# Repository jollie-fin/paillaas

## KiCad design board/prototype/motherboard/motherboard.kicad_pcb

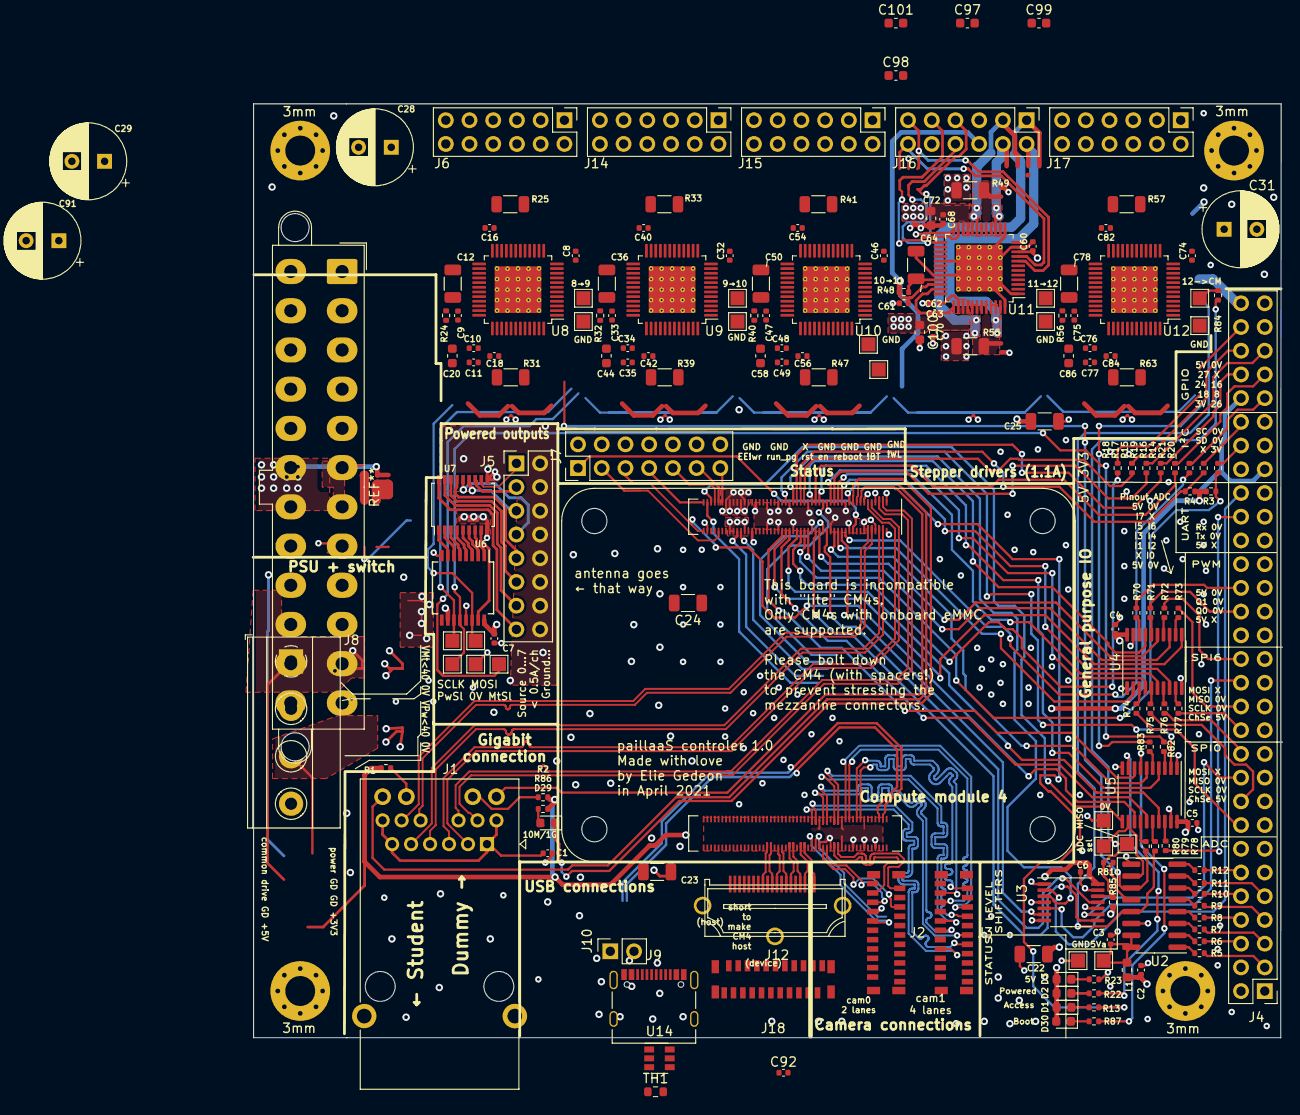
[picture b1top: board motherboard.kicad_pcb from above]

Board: 4 copper layers, 110.0 x 100.0 mm, 177 parts (0 on the bottom side), 260 nets.

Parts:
C1, C2, C3, C4, C5, C6, C7, C8, C11, C16, C18, C32, C35, C40, C42, C46, C49, C54, C56, C60, C63, C68, C70, C74, C77, C82, C84: 100n; C_0402_1005Metric
C9, C33, C47, C61, C75: 1u; C_0402_1005Metric
C10, C34, C48, C62, C76: 22n; C_0402_1005Metric
C12, C22, C23, C24, C25, C36, C50, C64, C78: 10u; C_1206_3216Metric
C20, C44, C58, C72, C86, C97, C98, C99, C100, C101: 1u; C_0603_1608Metric
C28, C29, C31, C91: 100u; CP_Radial_D8.0mm_P3.50mm
C92: 10n; C_0402_1005Metric
D1: GREEN; LED_0603_1608Metric
D2: RED; LED_0603_1608Metric
D3: BLUE; LED_0603_1608Metric
D29: LED; LED_0603_1608Metric
D30: YELLOW; LED_0603_1608Metric
H1, H2, H3, H4: MountingHole_Pad; MountingHole_3.2mm_M3_Pad_Via
J1: JK0654218Z; RJ45_Pulse_JK0654219NL_Horizontal
J2, J3, J18: Conn_01x22_MountingPin; 5019512230_1x22-1MP_P0.5mm_Vertical
J4: Conn_02x30_Odd_Even; PinHeader_2x30_P2.54mm_Vertical
J5: Conn_02x08_Odd_Even; PinHeader_2x08_P2.54mm_Vertical
J6, J14, J15, J16, J17: pin_header_02x06; PinHeader_2x06_P2.54mm_Vertical
J7: Conn_02x07_Odd_Even; PinHeader_2x07_P2.54mm_Vertical
J8: Conn_01x04; TerminalBlock_Phoenix_MKDS-1,5-4-5.08_1x04_P5.08mm_Horizont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
J9: USB_C_Receptacle_USB2.0; USB_C_Receptacle_Palconn_UTC16-G
J10: Conn_01x02; PinSocket_1x02_P2.54mm_Vertical
J12: HDMI_A; HDMI_vertical_476591102
L1: 15uH; L_0603_1608Metric
R1, R2, R86: 470; R_0402_1005Metric
R3, R4: 1K8; R_0402_1005Metric
R5, R6, R7, R8, R9, R10, R11, R12, R14, R15, R16, R17, R18, R19, R20, R21, R70, R71, R72, R73, R74, R75, R76, R77, R78: 100; R_0402_1005Metric
R13, R22, R23, R87: 4K7; R_0402_1005Metric
R24, R32, R40, R48, R56: 10; R_0402_1005Metric
R25, R31, R33, R39, R41, R47, R49, R55, R57, R63: 0.21; R_1206_3216Metric
R79, R80, R81, R82, R83, R84: 30; R_0402_1005Metric
R85: 10k; R_0402_1005Metric
TH1: Thermistor_PTC; R_0603_1608Metric
TP1, TP2, TP3, TP4, TP5, TP6, TP7, TP8, TP9, TP10, TP11, TP20, TP21, TP23, TP24, TP25, TP26, TP27, TP28, TP29: TestPoint; TestPoint_Pad_1.5x1.5mm
U1: Compute_Module_4_Functional; Raspberry-Pi-4-Compute-Module
U2: MCP3008; SOIC-16_3.9x9.9mm_P1.27mm
U3: 74LVC125; TSSOP-14_4.4x5mm_P0.65mm
U4, U5: 74HCT244; TSSOP-20_4.4x6.5mm_P0.65mm
U6: 74HC595; SSOP-16_5.3x6.2mm_P0.65mm
U7: TBD62783A; SSOP-18_4.4x6.5mm_P0.65mm
U8, U9, U10, U11, U12: TMC5130A-TA; TQFP-48-1EP_7x7mm_P0.5mm_EP5x5mm_ThermalVias
U14: SN65220; SOT-23-6

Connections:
+3V3: C6.1, C92.1, J2.22, J3.22, J4.45, J4.52, J18.22, R1.2, R2.2, R3.1, R4.1, R86.2, U1.78, U1.84, U1.86, U3.14
+5V: C2.1, C4.1, C5.1, C7.1, C8.1, C9.1, C22.1, C23.1, C24.1, C25.1, C32.1, C33.1, C46.1, C47.1, C60.1, C61.1, C74.1, C75.1, D1.2, D2.2, D3.2, D30.2, J4.2, J4.14, J4.15, J4.23, J4.32, J4.38, J4.40, J4.60, J6.6, J8.4, J10.1, J12.18, J14.6, J15.6, J16.6, J17.6, L1.2, R24.1, R32.1, R40.1, R48.1, R56.1, R85.1, U1.77, U1.79, U1.81, U1.83, U1.85, U1.87, U4.20, U5.20, U6.10, U6.16, U8.10, U8.34, U9.10, U9.34, U10.10, U10.34, U11.10, U11.34, U12.10, U12.34
/CAM_GPIO: J2.17, J3.17, U1.97
/GPIO/ACT_LED: R13.2, U1.21
/GPIO/AIN0: R5.1, U2.1
/GPIO/AIN0P: J4.3, R5.2
/GPIO/AIN1: R6.1, U2.2
/GPIO/AIN1P: J4.6, R6.2
/GPIO/AIN2: R7.1, U2.3
/GPIO/AIN2P: J4.5, R7.2
/GPIO/AIN3: R8.1, U2.4
/GPIO/AIN3P: J4.8, R8.2
/GPIO/AIN4: R9.1, U2.5
/GPIO/AIN4P: J4.7, R9.2
/GPIO/AIN5: R10.1, U2.6
/GPIO/AIN5P: J4.10, R10.2
/GPIO/AIN6: R11.1, U2.7
/GPIO/AIN6P: J4.9, R11.2
/GPIO/AIN7: R12.1, U2.8
/GPIO/AIN7P: J4.12, R12.2
/GPIO/AIN_SELECT_3V: U1.58, U5.8
/GPIO/AIN_SELECT_5V: TP5.1, U2.10, U5.12
/GPIO/CS0: U1.41, U4.17
/GPIO/CS0P: J4.16, R74.2
/GPIO/CS6: U1.56, U4.11
/GPIO/CS6P: J4.24, R77.2
/GPIO/GPIO8: R16.1, U1.39
/GPIO/GPIO8P: J4.53, R16.2
/GPIO/GPIO16: R15.1, U1.29
/GPIO/GPIO16P: J4.55, R15.2
/GPIO/GPIO18: R19.1, U1.49
/GPIO/GPIO18P: J4.54, R19.2
/GPIO/GPIO24: R17.1, U1.45
/GPIO/GPIO24P: J4.56, R17.2
/GPIO/GPIO26: R14.1, U1.24
/GPIO/GPIO26P: J4.51, R14.2
/GPIO/GPIO27: R18.1, U1.48
/GPIO/GPIO27P: J4.58, R18.2
/GPIO/MISO: R81.1, R84.2, R85.2, TP2.1, U3.12
/GPIO/MISO0: U1.40, U3.8
/GPIO/MISO0P: J4.20, U3.9
/GPIO/MISO4_3V: U1.34, U3.11
/GPIO/MISO6: U1.26, U3.6
/GPIO/MISO6P: J4.28, U3.5
/GPIO/MOSI: R80.2, TP4.1, U2.11, U6.14, U8.5
/GPIO/MOSI0: U1.44, U4.13
/GPIO/MOSI0P: J4.22, R76.2
/GPIO/MOSI4_3V: U1.30, U5.6
/GPIO/MOSI6: U1.27, U4.6
/GPIO/MOSI6P: J4.30, R72.2
/GPIO/MOTOR_SELECT: R83.2, TP7.1, U8.3, U9.3, U10.3, U11.3, U12.3
/GPIO/MOTOR_SELECT_3V: U1.54, U5.15
/GPIO/POWERED: R22.2, U5.9
/GPIO/POWER_SELECT: R82.2, TP21.1, U6.12
/GPIO/POWER_SELECT_3V: U1.50, U5.17
/GPIO/PWM0: U1.31, U4.4
/GPIO/PWM0P: J4.34, R71.2
/GPIO/PWM1: U1.28, U4.2
/GPIO/PWM1P: J4.36, R70.2
/GPIO/RxD0: U1.51, U3.3
/GPIO/RxD0P: J4.44, U3.2
/GPIO/SCL6: R4.2, R21.1, U1.47
/GPIO/SCL6P: J4.50, R21.2
/GPIO/SCLK: R79.2, TP3.1, U2.13, U6.11, U8.4, U9.4, U10.4, U11.4, U12.4
/GPIO/SCLK0: U1.38, U4.15
/GPIO/SCLK0P: J4.18, R75.2
/GPIO/SCLK4_3V: U1.37, U5.4
/GPIO/SCLK6: U1.25, U4.8
/GPIO/SCLK6P: J4.26, R73.2
/GPIO/SDA6: R3.2, R20.1, U1.46
/GPIO/SDA6P: J4.48, R20.2
/GPIO/TxD0: U1.55, U5.2
/GPIO/TxD0P: J4.42, R78.2
/GPIO/nEXTRST: J7.5, U1.100, U5.13
/GPIO/nEXTRST_pow: R87.2, U5.7
/SCL0: J3.20, J18.20, U1.80
/SCL1: J2.20, U1.35
/SDA0: J3.21, J18.21, U1.82
/SDA1: J2.21, U1.36
/camera/CAM0C+: J2.9, U1.142
/camera/CAM0C-: J2.8, U1.140
/camera/CAM0D0+: J2.3, U1.130
/camera/CAM0D0-: J2.2, U1.128
/camera/CAM0D1+: J2.6, U1.136
/camera/CAM0D1-: J2.5, U1.134
/camera/CAM1C+: J3.9, U1.129
/camera/CAM1C-: J3.8, U1.127
/camera/CAM1D0+: J3.3, U1.117
/camera/CAM1D0-: J3.2, U1.115
/camera/CAM1D1+: J3.6, U1.123
/camera/CAM1D1-: J3.5, U1.121
/camera/CAM1D2+: J3.12, U1.135
/camera/CAM1D2-: J3.11, U1.133
/camera/CAM1D3+: J3.15, U1.141
/camera/CAM1D3-: J3.14, U1.139
/cm4/BT_disable: J7.11, U1.91
/cm4/EEPROMprotect: J7.1, U1.20
/cm4/LED_Pwr: U1.95, U5.11
/cm4/USB+: J9.A6, J9.B6, U1.105, U14.6
/cm4/USB-: J9.A7, J9.B7, U1.103, U14.4
/cm4/WL_disable: J7.13, U1.89
/cm4/global_en: J7.7, U1.99
/cm4/rpireboot: J7.9, U1.93
/cm4/run_pg: J7.3, U1.92
/display/DSI1C+: J18.9, U1.189
/display/DSI1C-: J18.8, U1.187
/display/DSI1D0+: J18.3, U1.177
/display/DSI1D0-: J18.2, U1.175
/display/DSI1D1+: J18.6, U1.183
/display/DSI1D1-: J18.5, U1.181
/display/DSI1D2+: J18.12, U1.194
/display/DSI1D2-: J18.11, U1.193
/display/DSI1D3+: J18.15, U1.196
/display/DSI1D3-: J18.14, U1.195
/display/HDMI_0+: J12.7, U1.158
/display/HDMI_0-: J12.9, U1.160
/display/HDMI_1+: J12.4, U1.152
/display/HDMI_1-: J12.6, U1.154
/display/HDMI_2+: J12.1, U1.146
/display/HDMI_2-: J12.3, U1.148
/display/HDMI_C+: J12.10, U1.164
/display/HDMI_C-: J12.12, U1.166
/display/HDMI_CEC: J12.13, U1.149
/display/HDMI_HOT: J12.19, U1.143
/display/HDMI_SCL: J12.16, U1.147
/display/HDMI_SDA: J12.15, U1.145
/ethernet/ETH_0+: J1.11, U1.12
/ethernet/ETH_0-: J1.10, U1.10
/ethernet/ETH_1+: J1.4, U1.4
/ethernet/ETH_1-: J1.5, U1.6
/ethernet/ETH_2+: J1.3, U1.11
/ethernet/ETH_2-: J1.2, U1.9
/ethernet/ETH_3+: J1.8, U1.3
/ethernet/ETH_3-: J1.9, U1.5
/ethernet/ETH_LED_green: J1.13, U1.15
/ethernet/ETH_LED_yellow: J1.16, U1.17
/powerIO/OUT0: U6.15, U7.8
/powerIO/OUT1: U6.1, U7.7
/powerIO/OUT2: U6.2, U7.6
/powerIO/OUT3: U6.3, U7.5
/powerIO/OUT4: U6.4, U7.4
/powerIO/OUT5: U6.5, U7.3
/powerIO/OUT6: U6.6, U7.2
/powerIO/OUT7: U6.7, U7.1
/powerIO/SRC0: J5.15, U7.18
/powerIO/SRC1: J5.13, U7.17
/powerIO/SRC2: J5.11, U7.16
/powerIO/SRC3: J5.9, U7.15
/powerIO/SRC4: J5.7, U7.14
/powerIO/SRC5: J5.5, U7.13
/powerIO/SRC6: J5.3, U7.12
/powerIO/SRC7: J5.1, U7.11
/powerIO/motorU8/BRA: R31.1, U8.44
/powerIO/motorU8/BRB: R25.1, U8.17
/powerIO/motorU8/ENCA: J6.8, U8.25
/powerIO/motorU8/ENCB: J6.7, U8.24
/powerIO/motorU8/ENCN: J6.9, U8.23
/powerIO/motorU8/FILTERED_5V: C12.2, R24.2, U8.33
/powerIO/motorU8/LIMITL: J6.11, U8.8
/powerIO/motorU8/LIMITR: J6.12, U8.9
/powerIO/motorU8/MISO: TP8.1, U8.7, U9.5
/powerIO/motorU8/MOT_A1: J6.2, U8.46
/powerIO/motorU8/MOT_A2: J6.1, U8.42
/powerIO/motorU8/MOT_B1: J6.4, U8.15
/powerIO/motorU8/MOT_B2: J6.3, U8.19
/powerIO/motorU9/BRA: R39.1, U9.44
/powerIO/motorU9/BRB: R33.1, U9.17
/powerIO/motorU9/ENCA: J14.8, U9.25
/powerIO/motorU9/ENCB: J14.7, U9.24
/powerIO/motorU9/ENCN: J14.9, U9.23
/powerIO/motorU9/FILTERED_5V: C36.2, R32.2, U9.33
/powerIO/motorU9/LIMITL: J14.11, U9.8
/powerIO/motorU9/LIMITR: J14.12, U9.9
/powerIO/motorU9/MISO: TP10.1, U9.7, U10.5
/powerIO/motorU9/MOT_A1: J14.2, U9.46
/powerIO/motorU9/MOT_A2: J14.1, U9.42
/powerIO/motorU9/MOT_B1: J14.4, U9.15
/powerIO/motorU9/MOT_B2: J14.3, U9.19
/powerIO/motorU10/BRA: R47.1, U10.44
/powerIO/motorU10/BRB: R41.1, U10.17
/powerIO/motorU10/ENCA: J15.8, U10.25
/powerIO/motorU10/ENCB: J15.7, U10.24
/powerIO/motorU10/ENCN: J15.9, U10.23
/powerIO/motorU10/FILTERED_5V: C50.2, R40.2, U10.33
/powerIO/motorU10/LIMITL: J15.11, U10.8
/powerIO/motorU10/LIMITR: J15.12, U10.9
/powerIO/motorU10/MISO: TP23.1, U10.7, U11.5
/powerIO/motorU10/MOT_A1: J15.2, U10.46
/powerIO/motorU10/MOT_A2: J15.1, U10.42
/powerIO/motorU10/MOT_B1: J15.4, U10.15
/powerIO/motorU10/MOT_B2: J15.3, U10.19
/powerIO/motorU11/BRA: R55.1, U11.44
/powerIO/motorU11/BRB: R49.1, U11.17
/powerIO/motorU11/ENCA: J16.8, U11.25
/powerIO/motorU11/ENCB: J16.7, U11.24
/powerIO/motorU11/ENCN: J16.9, U11.23
/powerIO/motorU11/FILTERED_5V: C64.2, R48.2, U11.33
/powerIO/motorU11/LIMITL: J16.11, U11.8
/powerIO/motorU11/LIMITR: J16.12, U11.9
/powerIO/motorU11/MISO: TP25.1, U11.7, U12.5
/powerIO/motorU11/MOT_A1: J16.2, U11.46
/powerIO/motorU11/MOT_A2: J16.1, U11.42
/powerIO/motorU11/MOT_B1: J16.4, U11.15
/powerIO/motorU11/MOT_B2: J16.3, U11.19
/powerIO/motorU13/BRA: R63.1, U12.44
/powerIO/motorU13/BRB: R57.1, U12.17
/powerIO/motorU13/ENCA: J17.8, U12.25
/powerIO/motorU13/ENCB: J17.7, U12.24
/powerIO/motorU13/ENCN: J17.9, U12.23
/powerIO/motorU13/FILTERED_5V: C78.2, R56.2, U12.33
/powerIO/motorU13/LIMITL: J17.11, U12.8
/powerIO/motorU13/LIMITR: J17.12, U12.9
/powerIO/motorU13/MISO: R84.1, TP27.1, U12.7
/powerIO/motorU13/MOT_A1: J17.2, U12.46
/powerIO/motorU13/MOT_A2: J17.1, U12.42
/powerIO/motorU13/MOT_B1: J17.4, U12.15
/powerIO/motorU13/MOT_B2: J17.3, U12.19
GND: C1.2, C2.2, C3.2, C4.2, C5.2, C6.2, C7.2, C8.2, C9.2, C12.1, C16.2, C18.2, C20.2, C22.2, C23.2, C24.2, C25.2, C28.2, C29.2, C31.2, C32.2, C33.2, C36.1, C40.2, C42.2, C44.2, C46.2, C47.2, C50.1, C54.2, C56.2, C58.2, C60.2, C61.2, C64.1, C68.2, C70.2, C72.2, C74.2, C75.2, C78.1, C82.2, C84.2, C86.2, C91.2, C92.2, C97.2, C98.2, C99.2, C100.2, C101.2, H1.1, H2.1, H3.1, H4.1, J1.SH, J2.1, J2.4, J2.7, J2.10, J2.13, J2.16, J2.19, J2.MP, J3.1, J3.4, J3.7, J3.10, J3.13, J3.16, J3.19, J3.MP, J4.1, J4.13, J4.17, J4.19, J4.25, J4.27, J4.33, J4.35, J4.37, J4.41, J4.43, J4.47, J4.49, J4.59, J5.2, J5.4, J5.6, J5.8, J5.10, J5.12, J5.14, J5.16, J6.5, J7.2, J7.4, J7.8, J7.10, J7.12, J7.14, J8.2, J8.3, J9.A1, J9.A12, J9.B1, J9.B12, J9.S1, J12.2, J12.5, J12.8, J12.11, J12.17, J12.SH, J14.5, J15.5, J16.5, J17.5, J18.1, J18.4, J18.7, J18.10, J18.13, J18.16, J18.19, J18.MP, R23.2, R25.2, R31.2, R33.2, R39.2, R41.2, R47.2, R49.2, R55.2, R57.2, R63.2, TP6.1, TP9.1, TP11.1, TP20.1, TP24.1, TP26.1, TP28.1, TP29.1, U1.1, U1.2, U1.7, U1.8, U1.13, U1.14, U1.22, U1.23, U1.32, U1.33, U1.42, U1.43, U1.52, U1.53, U1.59, U1.60, U1.65, U1.66, U1.71, U1.74, U1.98, U1.101, U1.107, U1.108, U1.113, U1.114, U1.119, U1.120, U1.125, U1.126, U1.131, U1.132, U1.137, U1.138, U1.144, U1.150, U1.155, U1.156, U1.161, U1.162, U1.167, U1.168, U1.173, U1.174, U1.179, U1.180, U1.185, U1.186, U1.191, U1.192, U1.197, U1.198, U2.9, U2.14, U3.1, U3.4, U3.7, U3.10, U3.13, U4.1, U4.10, U4.19, U5.1, U5.10, U5.19, U6.8, U6.13, U7.10, U8.1, U8.11, U8.13, U8.29, U8.32, U8.48, U8.49, U9.1, U9.11, U9.13, U9.29, U9.32, U9.48, U9.49, U10.1, U10.11, U10.13, U10.29, U10.32, U10.48, U10.49, U11.1, U11.11, U11.13, U11.29, U11.32, U11.48, U11.49, U12.1, U12.11, U12.13, U12.29, U12.32, U12.48, U12.49, U14.2, U14.5
unnamed: C1.1, J1.1, J1.6, J1.7, J1.12
unnamed: C3.1, L1.1, TP1.1, U2.15, U2.16
unnamed: C10.1, U8.37
unnamed: C10.2, U8.35
unnamed: C11.1, U8.38
unnamed: C34.1, U9.37
unnamed: C34.2, U9.35
unnamed: C35.1, U9.38
unnamed: C48.1, U10.37
unnamed: C48.2, U10.35
unnamed: C49.1, U10.38
unnamed: C62.1, U11.37
unnamed: C62.2, U11.35
unnamed: C63.1, U11.38
unnamed: C76.1, U12.37
unnamed: C76.2, U12.35
unnamed: C77.1, U12.38
unnamed: D1.1, R13.1
unnamed: D2.1, R22.1
unnamed: D3.1, R23.1
unnamed: D29.1, U1.19
unnamed: D29.2, R86.1
unnamed: D30.1, R87.1
unnamed: J1.14, R2.1
unnamed: J1.15, R1.1
unnamed: J9.A4, J9.A9, J9.B4, J9.B9, TH1.1
unnamed: J10.2, TH1.2
unnamed: R70.1, U4.18
unnamed: R71.1, U4.16
unnamed: R72.1, U4.14
unnamed: R73.1, U4.12
unnamed: R74.1, U4.3
unnamed: R75.1, U4.5
unnamed: R76.1, U4.7
unnamed: R77.1, U4.9
unnamed: R78.1, U5.18
unnamed: R79.1, U5.16
unnamed: R80.1, U5.14
unnamed: R81.2, U2.12
unnamed: R82.1, U5.3
unnamed: R83.1, U5.5
VS: C11.2, C16.1, C18.1, C20.1, C28.1, C29.1, C31.1, C35.2, C40.1, C42.1, C44.1, C49.2, C54.1, C56.1, C58.1, C63.2, C68.1, C70.1, C72.1, C77.2, C82.1, C84.1, C86.1, C91.1, C97.1, C98.1, C99.1, C100.1, C101.1, J8.1, U7.9, U8.21, U8.39, U8.40, U9.21, U9.39, U9.40, U10.21, U10.39, U10.40, U11.21, U11.39, U11.40, U12.21, U12.39, U12.40

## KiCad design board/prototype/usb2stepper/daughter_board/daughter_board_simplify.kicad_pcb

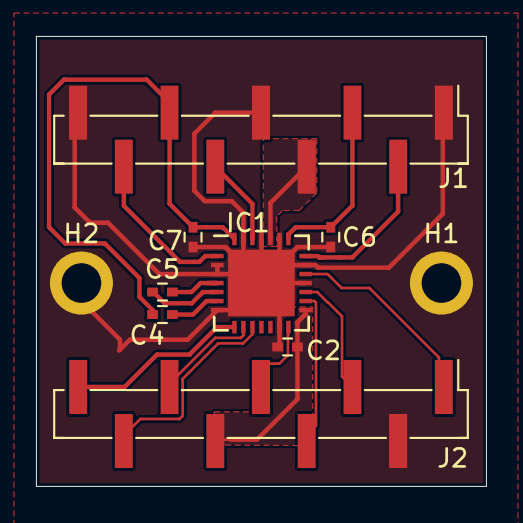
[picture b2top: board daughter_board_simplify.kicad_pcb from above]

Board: 2 copper layers, 25.0 x 25.0 mm, 10 parts (0 on the bottom side), 17 nets.

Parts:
C2, C4, C6, C7: 100n; C_0402
C5: 22n; C_0402
H1, H2: 2.5mm; MountingHole_2.2mm_M2_ISO7380_Pad
IC1: TMC2209-LA; QFN-28-1EP_5x5mm_Pitch0.5mm_EP3.7x3.7
J1, J2: Conn_01x09_Male; Pin_Header_Straight_1x09_Pitch2.54mm_SMD_Pin1Left

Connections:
+3V3: C2.2, IC1.15, J2.6
/5VOUT: IC1.8, J2.9
/DIR: IC1.19, J2.1
/MS1: IC1.9, J2.7
/MS2: IC1.10, J2.8
/OA1: IC1.24, J1.4
/OA2: IC1.21, J1.2
/OB1: IC1.26, J1.6
/OB2: IC1.1, J1.8
/STEP: IC1.16, J2.4
/UART: IC1.14, J2.5
/VREF: IC1.17, J2.3
GND: C2.1, C6.1, C7.1, H1.1, H2.1, IC1.2, IC1.3, IC1.7, IC1.13, IC1.18, IC1.20, IC1.23, IC1.25, IC1.27, IC1.29, J1.1, J1.5, J1.9, J2.2
unnamed: C4.1, IC1.6
unnamed: C5.1, IC1.5
unnamed: C5.2, IC1.4
Vdrive: C4.2, C6.2, C7.2, IC1.22, IC1.28, J1.3, J1.7
